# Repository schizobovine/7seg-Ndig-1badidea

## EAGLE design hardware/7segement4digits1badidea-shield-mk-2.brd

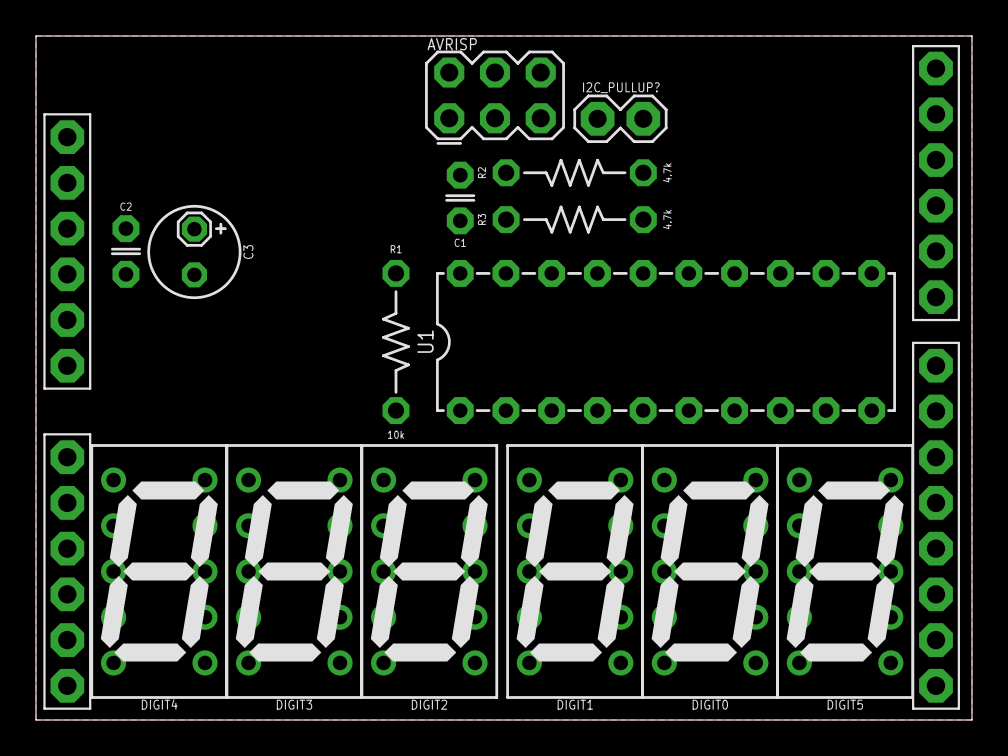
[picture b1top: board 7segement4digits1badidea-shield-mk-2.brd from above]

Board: 2 copper layers, 52.0 x 38.0 mm, 16 parts (0 on the bottom side), 21 nets, no tracks yet.

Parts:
AVRISP: AVR_SPI_PRG_6PTH; 2X3
C1: 0.1uF; C025-024X044
C2: 1uF; C025-024X044
C3: 10uF; E2,5-5
DIGIT0, DIGIT1, DIGIT2, DIGIT3, DIGIT4, DIGIT5: 7SEG_1DIGPTH-10MM; 7SEG_1DIG_10MM
I2C_PULLUP?: M02PTH; 1X02
R1: 10k; RESISTOR-AXIAL-PTH-7.68MM
R2, R3: 4.7k; RESISTOR-AXIAL-PTH-7.68MM
U1: ATTINY4213; DIL20
U2: ARDUINO_SHIELD_NOOUTLINE_INSIDE_SMALLER

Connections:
A: DIGIT0.10, DIGIT1.10, DIGIT2.10, DIGIT3.10, DIGIT4.10, DIGIT5.10, U1.2
B: DIGIT0.9, DIGIT1.9, DIGIT2.9, DIGIT3.9, DIGIT4.9, DIGIT5.9, U1.3
C: DIGIT0.8, DIGIT1.8, DIGIT2.8, DIGIT3.8, DIGIT4.8, DIGIT5.8, U1.4
D: DIGIT0.5, DIGIT1.5, DIGIT2.5, DIGIT3.5, DIGIT4.5, DIGIT5.5, U1.5
DIG0: DIGIT0.1, DIGIT0.6, U1.11
DIG1: DIGIT1.1, DIGIT1.6, U1.12
DIG2: DIGIT2.1, DIGIT2.6, U1.13
DIG3: DIGIT3.1, DIGIT3.6, U1.14
DIG4: DIGIT4.1, DIGIT4.6, U1.15
DIG5: DIGIT5.1, DIGIT5.6, U1.16
DP: DIGIT0.7, DIGIT1.7, DIGIT2.7, DIGIT3.7, DIGIT4.7, DIGIT5.7, U1.9
E: DIGIT0.4, DIGIT1.4, DIGIT2.4, DIGIT3.4, DIGIT4.4, DIGIT5.4, U1.6
F: DIGIT0.2, DIGIT1.2, DIGIT2.2, DIGIT3.2, DIGIT4.2, DIGIT5.2, U1.7
G: DIGIT0.3, DIGIT1.3, DIGIT2.3, DIGIT3.3, DIGIT4.3, DIGIT5.3, U1.8
GND: AVRISP.6, C1.2, C2.2, C3.-, U1.10, U2.GND@0, U2.GND@1
MISO: AVRISP.1, U1.18
MOSI/SDA: AVRISP.4, R2.P$1, U1.17, U2.A4
unnamed: R1.P$2, U1.1
unnamed: I2C_PULLUP?.2, R2.P$2, R3.P$2
SCK/SCL: AVRISP.3, R3.P$1, U1.19, U2.A5
VCC: AVRISP.2, C1.1, C2.1, C3.+, I2C_PULLUP?.1, R1.P$1, U1.20, U2.5V

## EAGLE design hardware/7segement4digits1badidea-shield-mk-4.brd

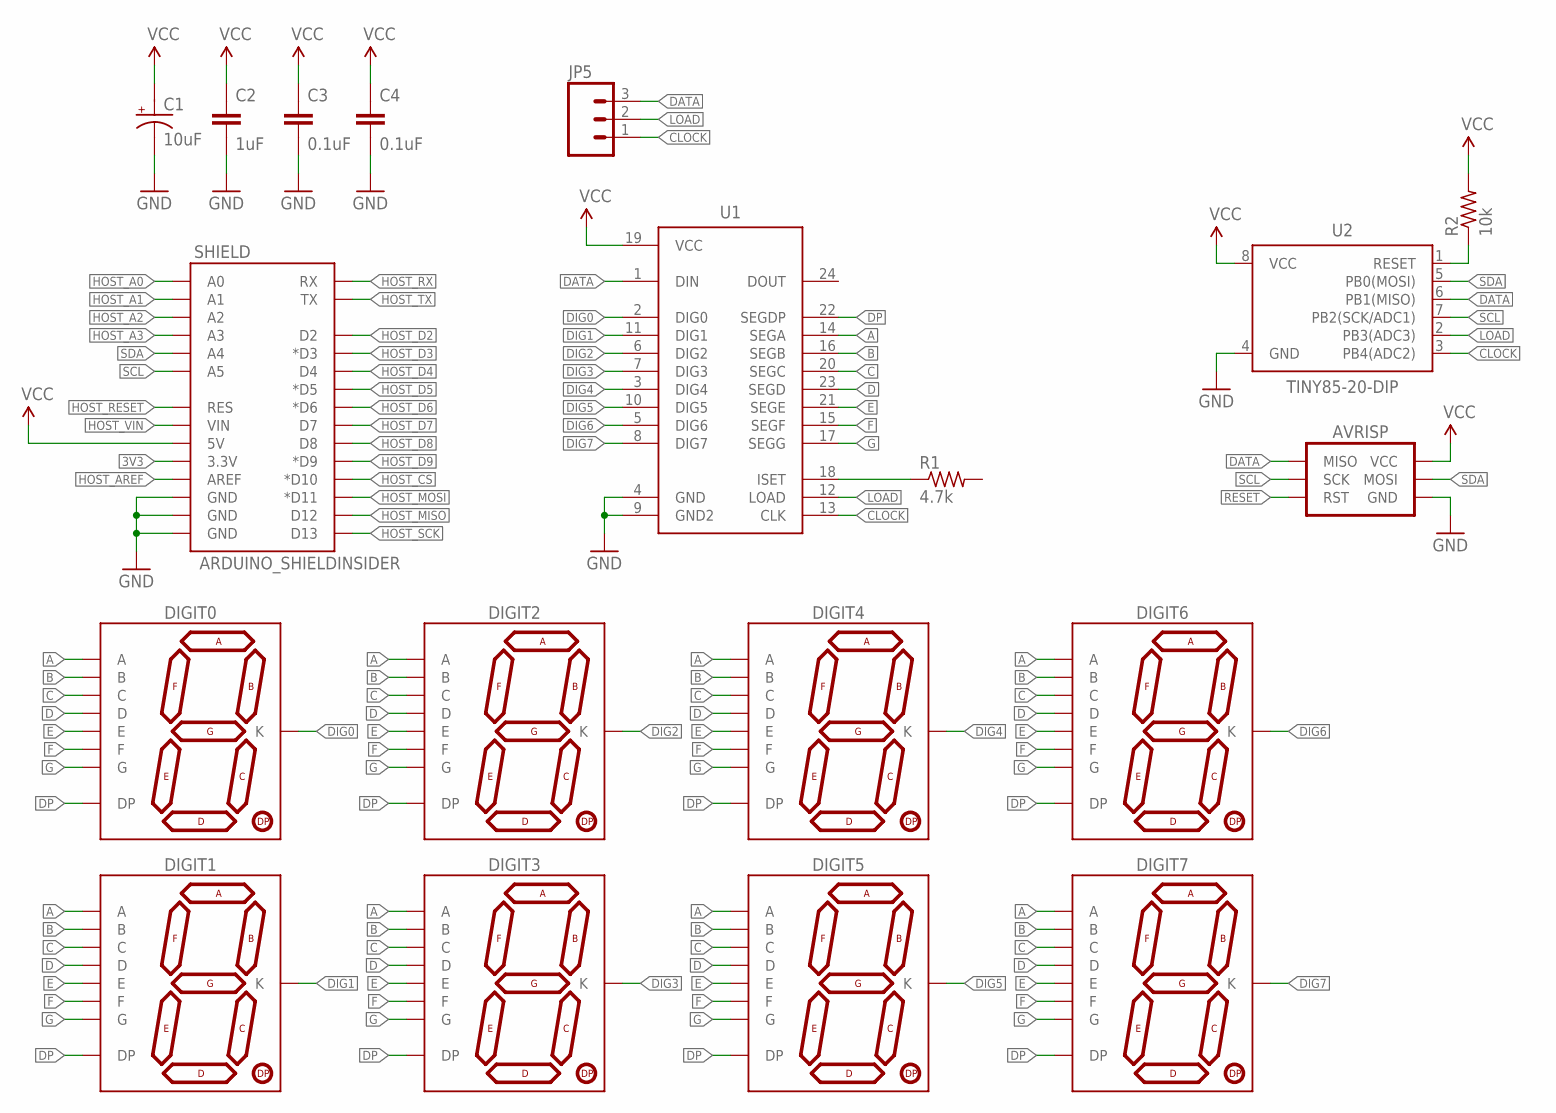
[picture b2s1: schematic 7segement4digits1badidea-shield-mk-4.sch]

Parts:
AVRISP: AVR_SPI_PRG_6PTH; 2X3
C1: 10uF; E2,5-5
C2: 1uF; C025-024X044
C3, C4: 0.1uF; C025-024X044
DIGIT0, DIGIT1, DIGIT2, DIGIT3, DIGIT4, DIGIT5, DIGIT6, DIGIT7: 7SEG_1DIGPTH-10MM; 7SEG_1DIG_10MM
JP5: M03PTH; 1X03
R1: 4.7k; RESISTOR-AXIAL-PTH-7.68MM
R2: 10k; RESISTOR-AXIAL-PTH-7.68MM
SHIELD: ARDUINO_SHIELDINSIDER; ARDUINO_SHIELD_NOOUTLINE_INSIDE
U1: MAX7219DIP; DIL24
U2: TINY85-20-DIP; DIP08

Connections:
3V3: SHIELD.3.3V
A: DIGIT0.10 (A), DIGIT1.10 (A), DIGIT2.10 (A), DIGIT3.10 (A), DIGIT4.10 (A), DIGIT5.10 (A), DIGIT6.10 (A), DIGIT7.10 (A), U1.14 (SEGA)
B: DIGIT0.9 (B), DIGIT1.9 (B), DIGIT2.9 (B), DIGIT3.9 (B), DIGIT4.9 (B), DIGIT5.9 (B), DIGIT6.9 (B), DIGIT7.9 (B), U1.16 (SEGB)
C: DIGIT0.8 (C), DIGIT1.8 (C), DIGIT2.8 (C), DIGIT3.8 (C), DIGIT4.8 (C), DIGIT5.8 (C), DIGIT6.8 (C), DIGIT7.8 (C), U1.20 (SEGC)
CLOCK: JP5.1, U1.13 (CLK), U2.3 (PB4(ADC2))
D: DIGIT0.5 (D), DIGIT1.5 (D), DIGIT2.5 (D), DIGIT3.5 (D), DIGIT4.5 (D), DIGIT5.5 (D), DIGIT6.5 (D), DIGIT7.5 (D), U1.23 (SEGD)
DATA: AVRISP.1 (MISO), JP5.3, U1.1 (DIN), U2.6 (PB1(MISO))
DIG0: DIGIT0.1 (K), DIGIT0.6 (K), U1.2 (DIG0)
DIG1: DIGIT1.1 (K), DIGIT1.6 (K), U1.11 (DIG1)
DIG2: DIGIT2.1 (K), DIGIT2.6 (K), U1.6 (DIG2)
DIG3: DIGIT3.1 (K), DIGIT3.6 (K), U1.7 (DIG3)
DIG4: DIGIT4.1 (K), DIGIT4.6 (K), U1.3 (DIG4)
DIG5: DIGIT5.1 (K), DIGIT5.6 (K), U1.10 (DIG5)
DIG6: DIGIT6.1 (K), DIGIT6.6 (K), U1.5 (DIG6)
DIG7: DIGIT7.1 (K), DIGIT7.6 (K), U1.8 (DIG7)
DP: DIGIT0.7 (DP), DIGIT1.7 (DP), DIGIT2.7 (DP), DIGIT3.7 (DP), DIGIT4.7 (DP), DIGIT5.7 (DP), DIGIT6.7 (DP), DIGIT7.7 (DP), U1.22 (SEGDP)
E: DIGIT0.4 (E), DIGIT1.4 (E), DIGIT2.4 (E), DIGIT3.4 (E), DIGIT4.4 (E), DIGIT5.4 (E), DIGIT6.4 (E), DIGIT7.4 (E), U1.21 (SEGE)
F: DIGIT0.2 (F), DIGIT1.2 (F), DIGIT2.2 (F), DIGIT3.2 (F), DIGIT4.2 (F), DIGIT5.2 (F), DIGIT6.2 (F), DIGIT7.2 (F), U1.15 (SEGF)
G: DIGIT0.3 (G), DIGIT1.3 (G), DIGIT2.3 (G), DIGIT3.3 (G), DIGIT4.3 (G), DIGIT5.3 (G), DIGIT6.3 (G), DIGIT7.3 (G), U1.17 (SEGG)
GND: AVRISP.6 (GND), C1.-, C2.2, C3.2, C4.2, SHIELD.GND@0 (GND), SHIELD.GND@1 (GND), SHIELD.GND@2 (GND), U1.4 (GND), U1.9 (GND2), U2.4 (GND)
HOST_A0: SHIELD.A0
HOST_A1: SHIELD.A1
HOST_A2: SHIELD.A2
HOST_A3: SHIELD.A3
HOST_AREF: SHIELD.AREF
HOST_CS: SHIELD.D10 (*D10)
HOST_D2: SHIELD.D2
HOST_D3: SHIELD.D3 (*D3)
HOST_D4: SHIELD.D4
HOST_D5: SHIELD.D5 (*D5)
HOST_D6: SHIELD.D6 (*D6)
HOST_D7: SHIELD.D7
HOST_D8: SHIELD.D8
HOST_D9: SHIELD.D9 (*D9)
HOST_MISO: SHIELD.D12
HOST_MOSI: SHIELD.D11 (*D11)
HOST_RESET: SHIELD.RES
HOST_RX: SHIELD.RX
HOST_SCK: SHIELD.D13
HOST_TX: SHIELD.TX
HOST_VIN: SHIELD.VIN
LOAD: JP5.2, U1.12 (LOAD), U2.2 (PB3(ADC3))
unnamed: R2.P$1 (1), U2.1 (RESET)
unnamed: R1.P$1 (1), U1.18 (ISET)
RESET: AVRISP.5 (RST)
SCL: AVRISP.3 (SCK), SHIELD.A5, U2.7 (PB2(SCK/ADC1))
SDA: AVRISP.4 (MOSI), SHIELD.A4, U2.5 (PB0(MOSI))
VCC: AVRISP.2 (VCC), C1.+, C2.1, C3.1, C4.1, R2.P$2 (2), SHIELD.5V, U1.19 (VCC), U2.8 (VCC)

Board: 2 copper layers, 19 parts (0 on the bottom side), 25 nets, no tracks yet.

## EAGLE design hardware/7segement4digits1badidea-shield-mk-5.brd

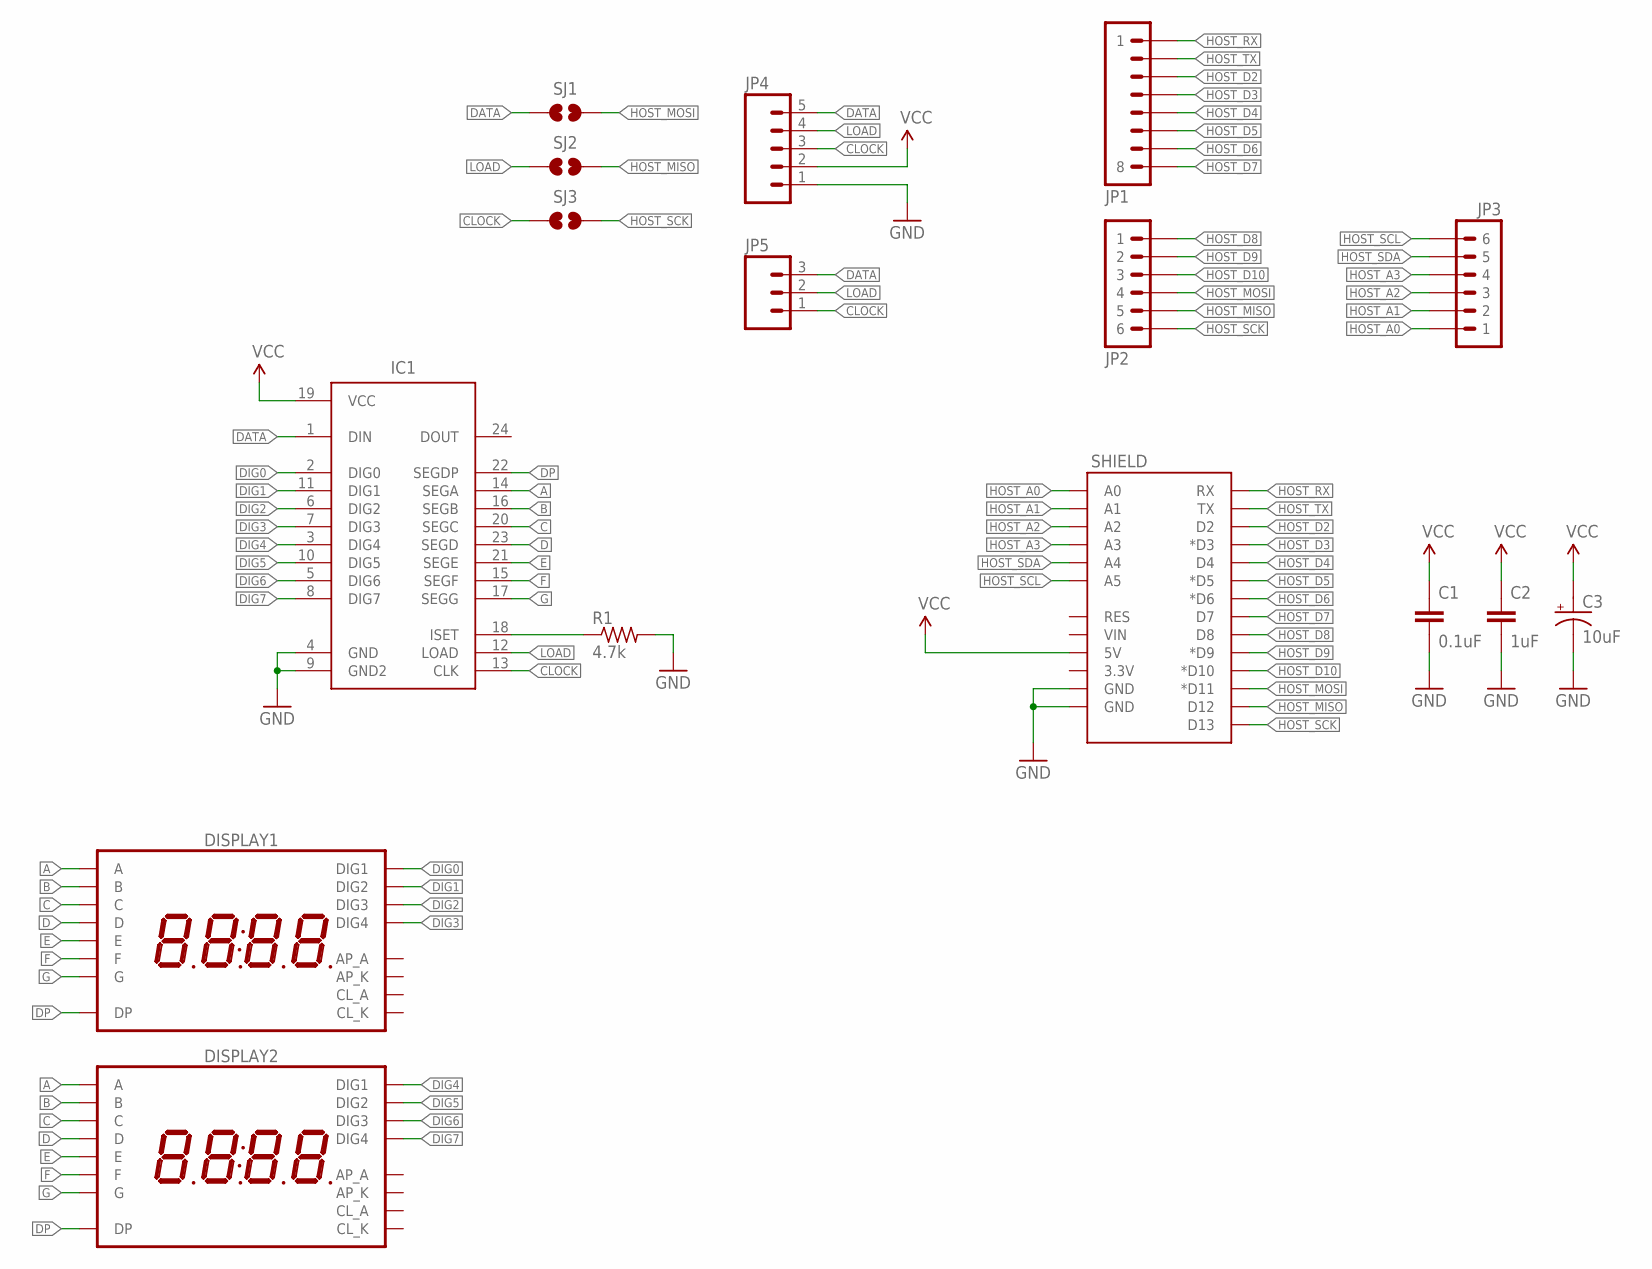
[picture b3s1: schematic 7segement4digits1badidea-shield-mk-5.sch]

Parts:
C1: 0.1uF; C025-024X044
C2: 1uF; C025-024X044
C3: 10uF; E2,5-6
DISPLAY1, DISPLAY2: 7SEG_4DIGIT_10MM; 7SEG_4DIG_10MM
IC1: MAX7219DIP; DIL24
JP1: M08NOT-SHITTY-NO-SILK; 1X08_NS
JP2, JP3: M06SIP; 1X06
JP4: M05PTH; 1X05
JP5: M031X03_NO_SILK; 1X03_NO_SILK
R1: 4.7k; RESISTOR-AXIAL-PTH-5.08MM
SHIELD: ARDUINO_SHIELD_SMALLERNEKKID; ARDUINO_SHIELD_SMALLER_NEKKID
SJ1, SJ2, SJ3: JUMPER-PAD-2-NOYES_SILK; PAD-JUMPER-2-NO_YES_SILK

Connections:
A: DISPLAY1.14 (A), DISPLAY2.14 (A), IC1.14 (SEGA)
B: DISPLAY1.16 (B), DISPLAY2.16 (B), IC1.16 (SEGB)
C: DISPLAY1.13 (C), DISPLAY2.13 (C), IC1.20 (SEGC)
CLOCK: IC1.13 (CLK), JP4.3, JP5.1, SJ3.1
D: DISPLAY1.3 (D), DISPLAY2.3 (D), IC1.23 (SEGD)
DATA: IC1.1 (DIN), JP4.5, JP5.3, SJ1.1
DIG0: DISPLAY1.1 (DIG1), IC1.2 (DIG0)
DIG1: DISPLAY1.2 (DIG2), IC1.11 (DIG1)
DIG2: DISPLAY1.6 (DIG3), IC1.6 (DIG2)
DIG3: DISPLAY1.8 (DIG4), IC1.7 (DIG3)
DIG4: DISPLAY2.1 (DIG1), IC1.3 (DIG4)
DIG5: DISPLAY2.2 (DIG2), IC1.10 (DIG5)
DIG6: DISPLAY2.6 (DIG3), IC1.5 (DIG6)
DIG7: DISPLAY2.8 (DIG4), IC1.8 (DIG7)
DP: DISPLAY1.7 (DP), DISPLAY2.7 (DP), IC1.22 (SEGDP)
E: DISPLAY1.5 (E), DISPLAY2.5 (E), IC1.21 (SEGE)
F: DISPLAY1.11 (F), DISPLAY2.11 (F), IC1.15 (SEGF)
G: DISPLAY1.15 (G), DISPLAY2.15 (G), IC1.17 (SEGG)
GND: C1.2, C2.2, C3.-, IC1.4 (GND), IC1.9 (GND2), JP4.1, R1.P$2 (2), SHIELD.GND@0 (GND), SHIELD.GND@1 (GND)
HOST_A0: JP3.1, SHIELD.A0
HOST_A1: JP3.2, SHIELD.A1
HOST_A2: JP3.3, SHIELD.A2
HOST_A3: JP3.4, SHIELD.A3
HOST_D2: JP1.3, SHIELD.D2
HOST_D3: JP1.4, SHIELD.D3 (*D3)
HOST_D4: JP1.5, SHIELD.D4
HOST_D5: JP1.6, SHIELD.D5 (*D5)
HOST_D6: JP1.7, SHIELD.D6 (*D6)
HOST_D7: JP1.8, SHIELD.D7
HOST_D8: JP2.1, SHIELD.D8
HOST_D9: JP2.2, SHIELD.D9 (*D9)
HOST_D10: JP2.3, SHIELD.D10 (*D10)
HOST_MISO: JP2.5, SHIELD.D12, SJ2.2
HOST_MOSI: JP2.4, SHIELD.D11 (*D11), SJ1.2
HOST_RX: JP1.1, SHIELD.RX
HOST_SCK: JP2.6, SHIELD.D13, SJ3.2
HOST_SCL: JP3.6, SHIELD.A5
HOST_SDA: JP3.5, SHIELD.A4
HOST_TX: JP1.2, SHIELD.TX
LOAD: IC1.12 (LOAD), JP4.4, JP5.2, SJ2.1
unnamed: IC1.18 (ISET), R1.P$1 (1)
VCC: C1.1, C2.1, C3.+, IC1.19 (VCC), JP4.2, SHIELD.5V

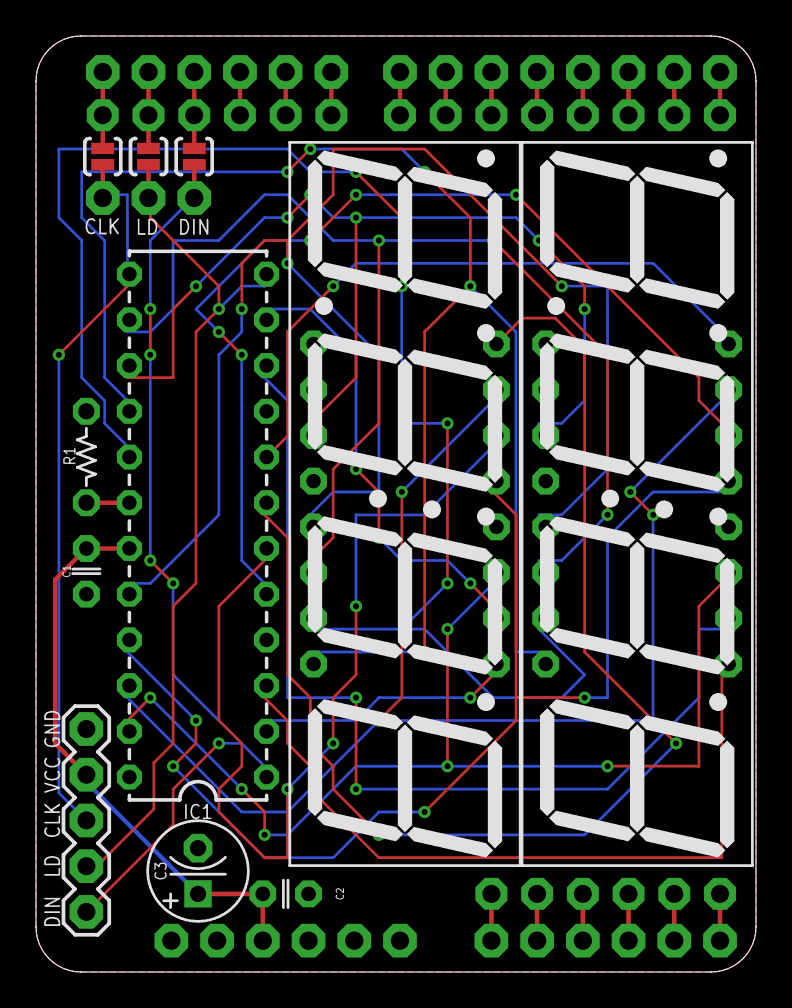
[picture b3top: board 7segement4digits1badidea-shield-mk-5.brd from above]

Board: 2 copper layers, 40.0 x 52.0 mm, 16 parts (0 on the bottom side), 42 nets.

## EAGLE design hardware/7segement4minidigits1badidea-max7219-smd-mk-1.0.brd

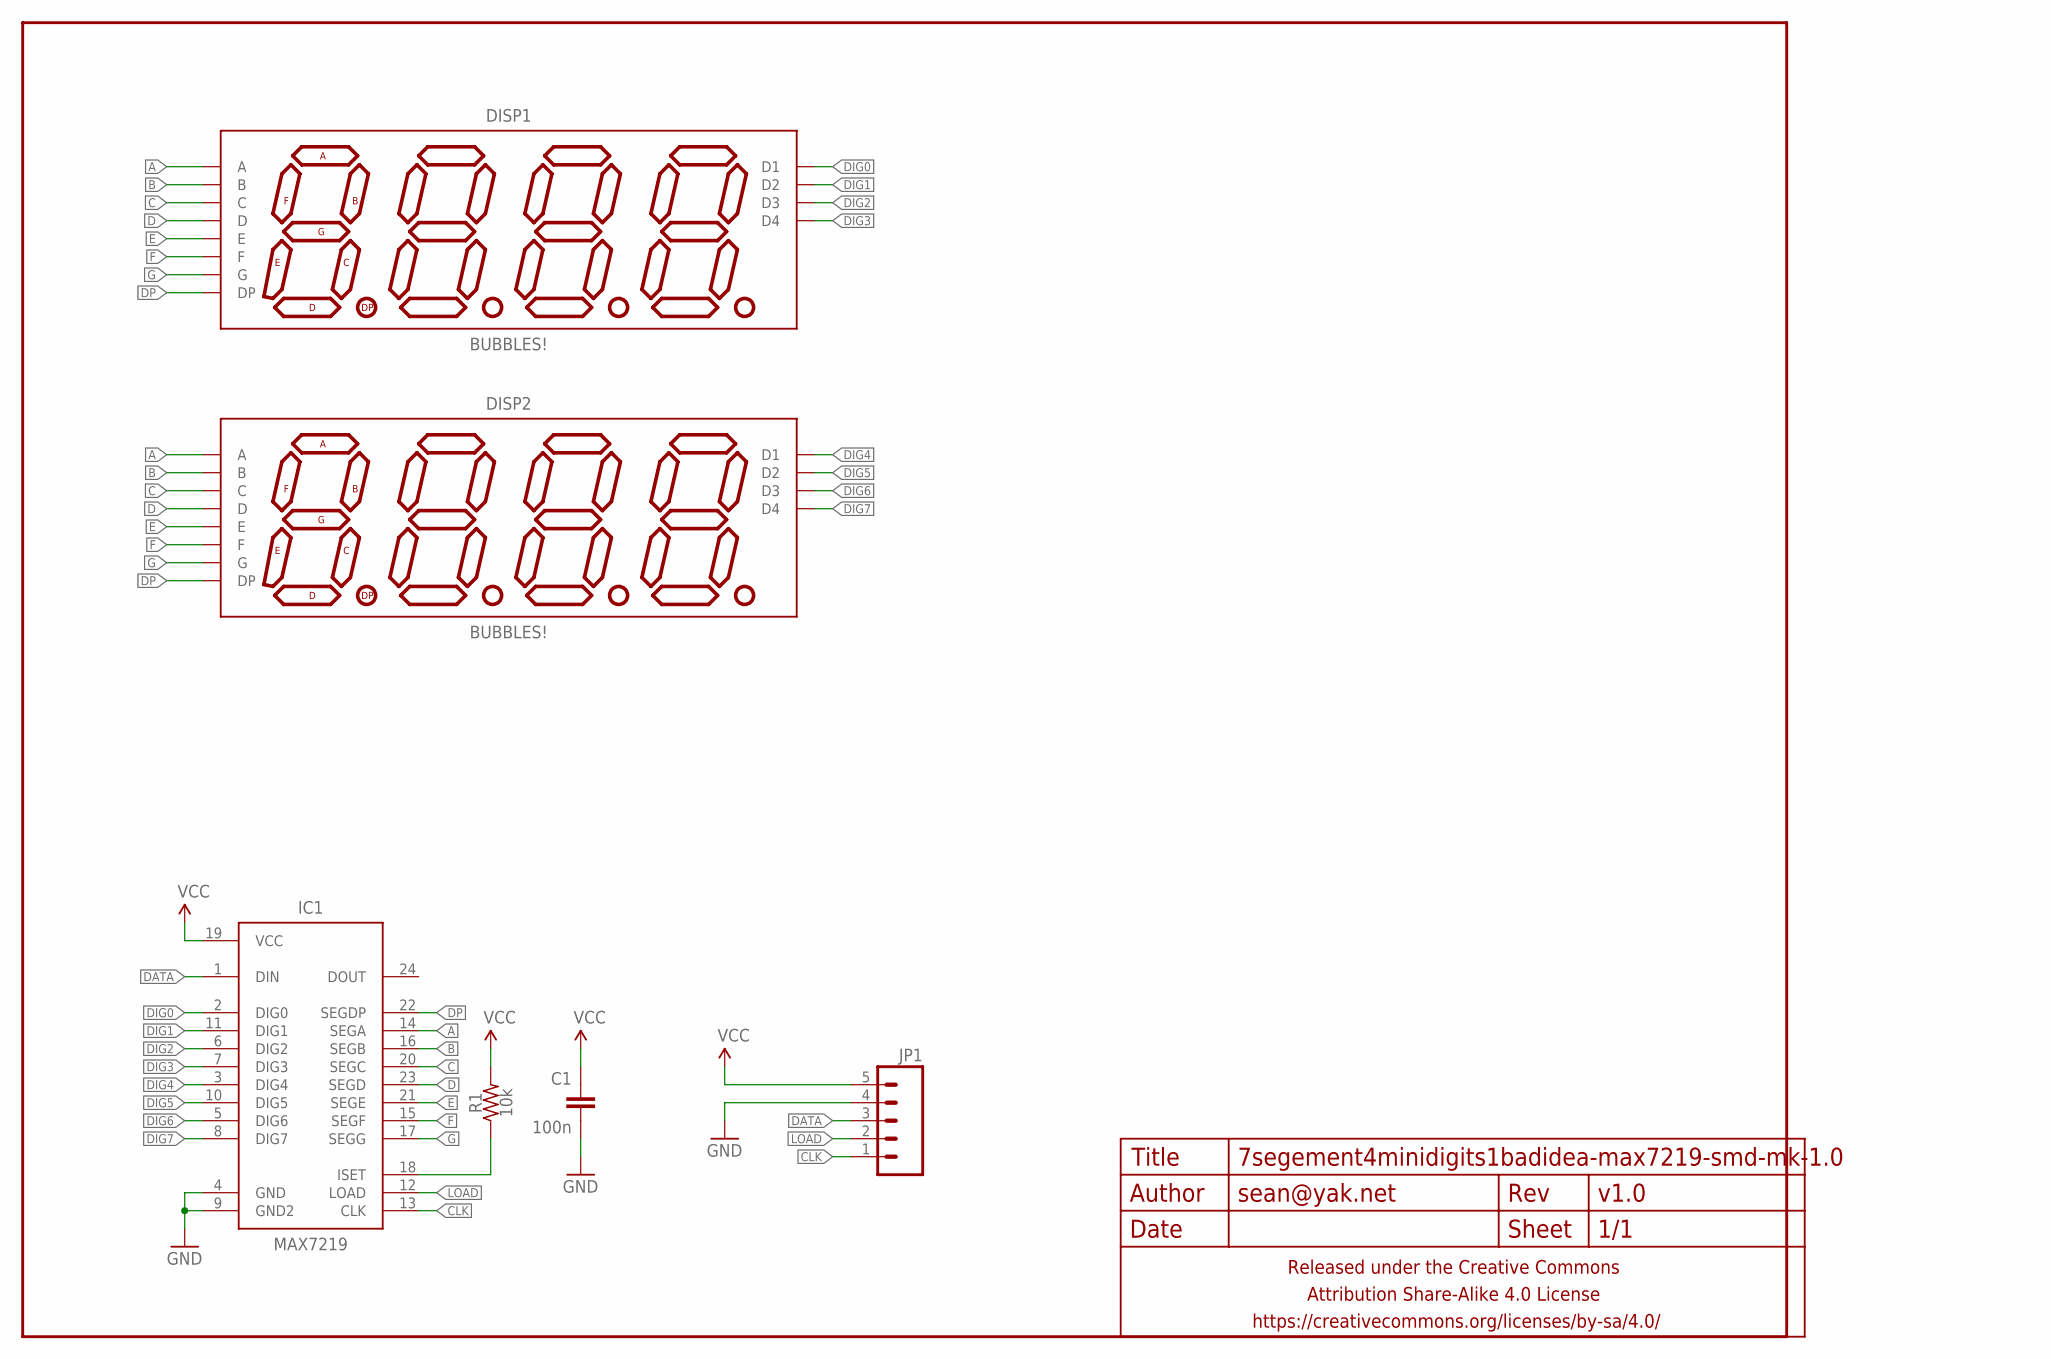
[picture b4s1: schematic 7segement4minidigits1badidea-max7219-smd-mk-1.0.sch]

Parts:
C1: 100n; C0603
DISP1, DISP2: BUBBLES!; DIL12
FRAME1: FRAME-LETTERNO_PACKAGE; DUMMY
IC1: MAX7219; SO24W
JP1: M05PTH-CENTERED; 1X05_PTH_CENTERED
R1: 10k; R0603

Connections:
A: DISP1.12 (A), DISP2.12 (A), IC1.14 (SEGA)
B: DISP1.11 (B), DISP2.11 (B), IC1.16 (SEGB)
C: DISP1.3 (C), DISP2.3 (C), IC1.20 (SEGC)
CLK: IC1.13 (CLK), JP1.1
D: DISP1.8 (D), DISP2.8 (D), IC1.23 (SEGD)
DATA: IC1.1 (DIN), JP1.3
DIG0: DISP1.1 (D1), IC1.2 (DIG0)
DIG1: DISP1.10 (D2), IC1.11 (DIG1)
DIG2: DISP1.4 (D3), IC1.6 (DIG2)
DIG3: DISP1.6 (D4), IC1.7 (DIG3)
DIG4: DISP2.1 (D1), IC1.3 (DIG4)
DIG5: DISP2.10 (D2), IC1.10 (DIG5)
DIG6: DISP2.4 (D3), IC1.5 (DIG6)
DIG7: DISP2.6 (D4), IC1.8 (DIG7)
DP: DISP1.5 (DP), DISP2.5 (DP), IC1.22 (SEGDP)
E: DISP1.2 (E), DISP2.2 (E), IC1.21 (SEGE)
F: DISP1.9 (F), DISP2.9 (F), IC1.15 (SEGF)
G: DISP1.7 (G), DISP2.7 (G), IC1.17 (SEGG)
GND: C1.2, IC1.4 (GND), IC1.9 (GND2), JP1.4
LOAD: IC1.12 (LOAD), JP1.2
unnamed: IC1.18 (ISET), R1.1
VCC: C1.1, IC1.19 (VCC), JP1.5, R1.2

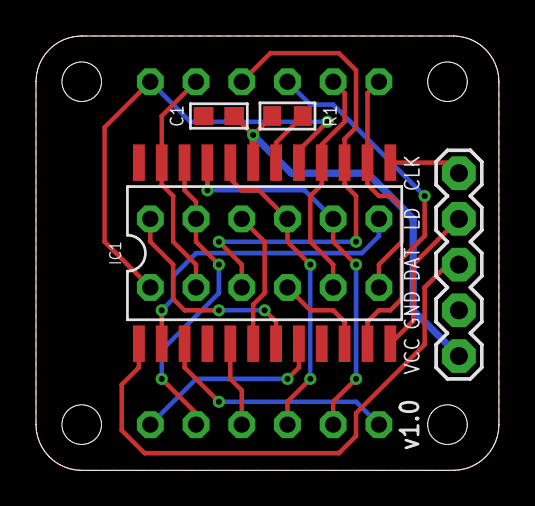
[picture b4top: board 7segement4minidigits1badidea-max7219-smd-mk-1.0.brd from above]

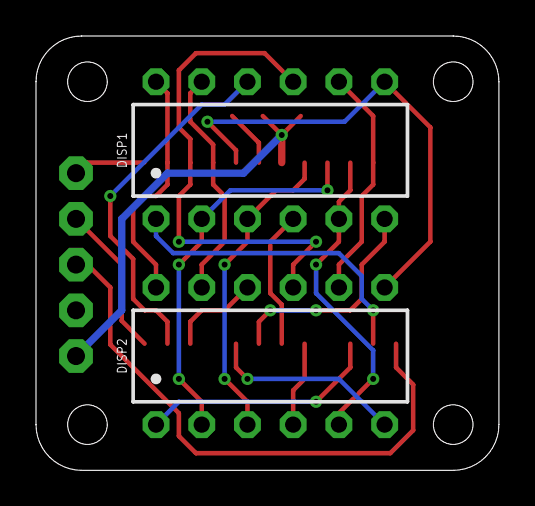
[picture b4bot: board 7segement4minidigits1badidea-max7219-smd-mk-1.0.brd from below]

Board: 2 copper layers, 25.7 x 24.1 mm, 7 parts (2 on the bottom side), 22 nets.

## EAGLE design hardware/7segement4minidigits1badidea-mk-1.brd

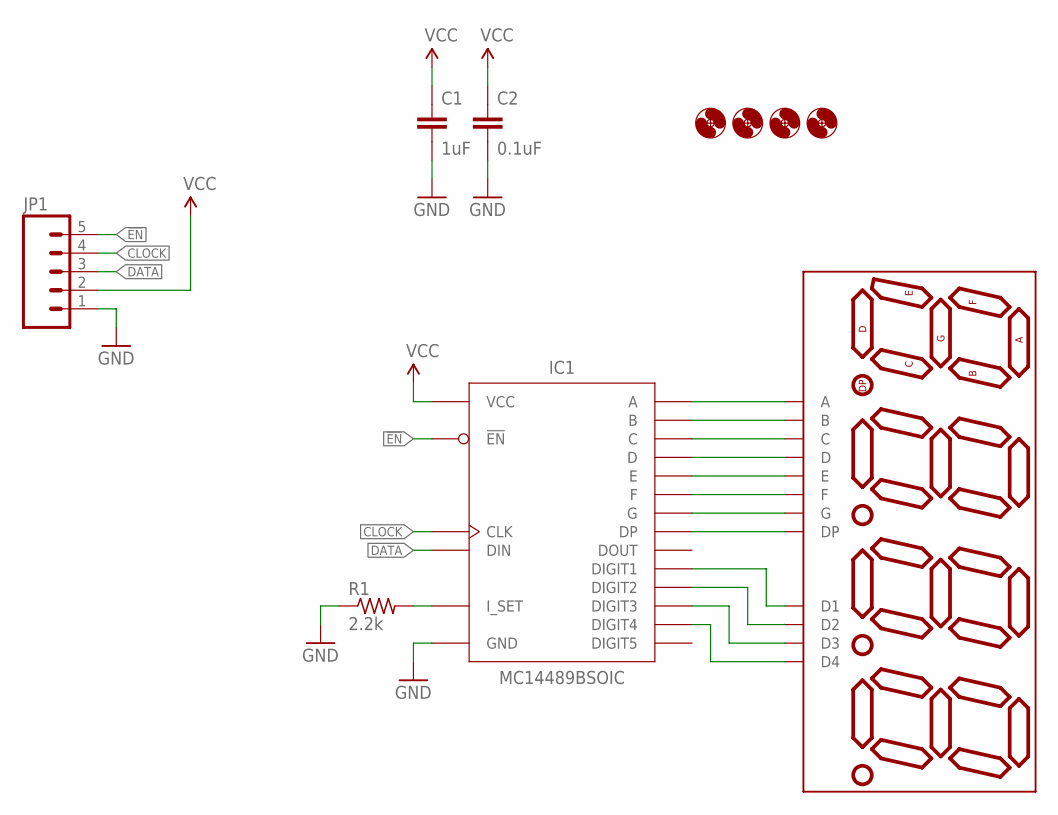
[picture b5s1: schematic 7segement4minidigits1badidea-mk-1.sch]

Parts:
C1: 1uF; C025-024X044
C2: 0.1uF; C025-024X044
DISP1: BUBBLES!; DIL12
H1, H2, H3, H4: HOLE#2; HOLE-#2
IC1: MC14489BSOIC; SOP20W
JP1: M05PTH; 1X05
R1: 2.2k; RESISTOR-AXIAL-PTH-5.08MM

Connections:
!EN: IC1.10 (!EN), JP1.5
CLOCK: IC1.11 (CLK), JP1.4
DATA: IC1.12 (DIN), JP1.3
GND: C1.2, C2.2, IC1.14 (GND), JP1.1, R1.P$1 (1)
unnamed: DISP1.12 (A), IC1.7 (A)
unnamed: DISP1.11 (B), IC1.6 (B)
unnamed: DISP1.3 (C), IC1.5 (C)
unnamed: DISP1.8 (D), IC1.4 (D)
unnamed: DISP1.2 (E), IC1.2 (E)
unnamed: DISP1.9 (F), IC1.1 (F)
unnamed: DISP1.7 (G), IC1.20 (G)
unnamed: DISP1.5 (DP), IC1.19 (DP)
unnamed: DISP1.1 (D1), IC1.9 (DIGIT1)
unnamed: DISP1.10 (D2), IC1.13 (DIGIT2)
unnamed: DISP1.4 (D3), IC1.15 (DIGIT3)
unnamed: DISP1.6 (D4), IC1.16 (DIGIT4)
unnamed: IC1.8 (I_SET), R1.P$2 (2)
VCC: C1.1, C2.1, IC1.3 (VCC), JP1.2

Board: 2 copper layers, 10 parts (1 on the bottom side), 18 nets, no tracks yet.

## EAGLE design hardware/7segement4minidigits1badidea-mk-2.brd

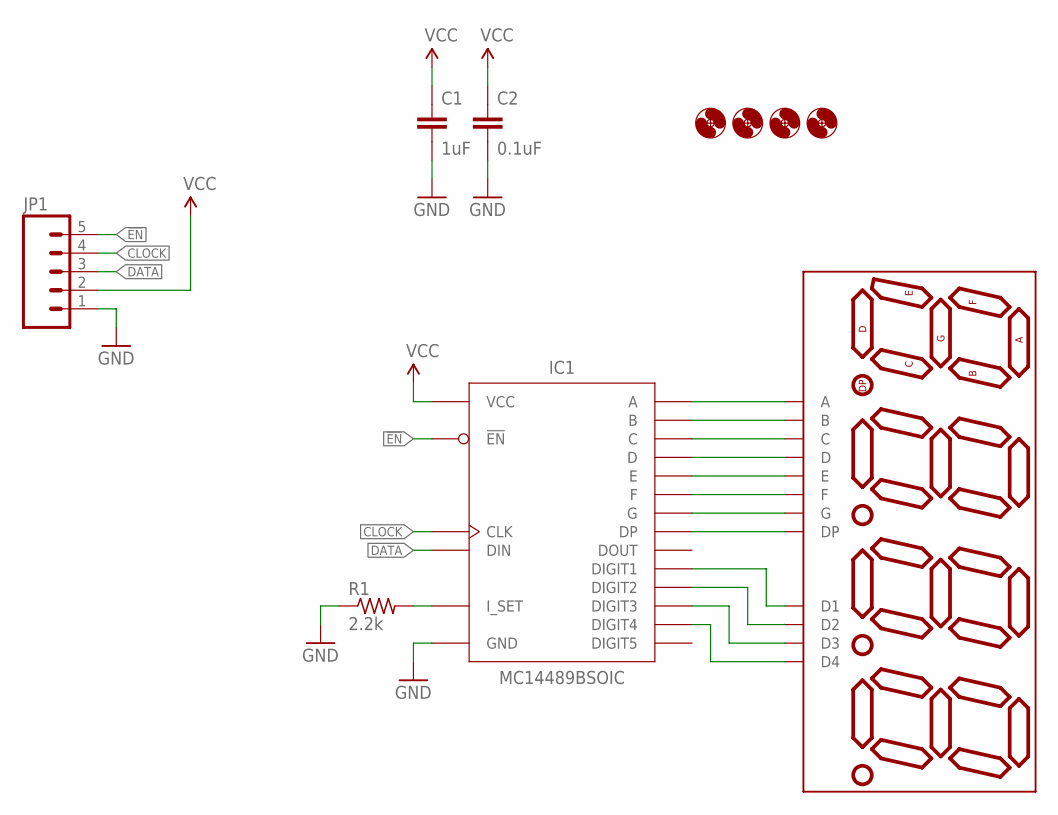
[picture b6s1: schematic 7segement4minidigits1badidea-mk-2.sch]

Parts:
BUBBLES!: (>^_^)>; DIP12-SMD-WAT
C1: 1uF; C0805
C2: 0.1uF; C0603
H1, H2, H3, H4: HOLE#2; HOLE-#2
IC1: MC14489BSOIC; SOP20W
JP1: M05PTH; 1X05
R1: 2.2k; R0603

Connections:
!EN: IC1.10 (!EN), JP1.5
CLOCK: IC1.11 (CLK), JP1.4
DATA: IC1.12 (DIN), JP1.3
GND: C1.2, C2.2, IC1.14 (GND), JP1.1, R1.1
unnamed: BUBBLES!.12 (A), IC1.7 (A)
unnamed: BUBBLES!.11 (B), IC1.6 (B)
unnamed: BUBBLES!.3 (C), IC1.5 (C)
unnamed: BUBBLES!.8 (D), IC1.4 (D)
unnamed: BUBBLES!.2 (E), IC1.2 (E)
unnamed: BUBBLES!.9 (F), IC1.1 (F)
unnamed: BUBBLES!.7 (G), IC1.20 (G)
unnamed: BUBBLES!.5 (DP), IC1.19 (DP)
unnamed: BUBBLES!.1 (D1), IC1.9 (DIGIT1)
unnamed: BUBBLES!.10 (D2), IC1.13 (DIGIT2)
unnamed: BUBBLES!.4 (D3), IC1.15 (DIGIT3)
unnamed: BUBBLES!.6 (D4), IC1.16 (DIGIT4)
unnamed: IC1.8 (I_SET), R1.2
VCC: C1.1, C2.1, IC1.3 (VCC), JP1.2

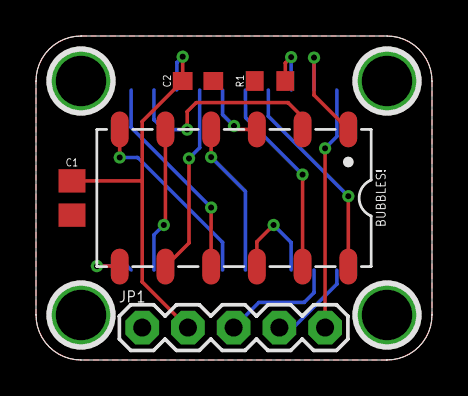
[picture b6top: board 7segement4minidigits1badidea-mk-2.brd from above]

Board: 2 copper layers, 22.0 x 18.0 mm, 10 parts (1 on the bottom side), 18 nets.

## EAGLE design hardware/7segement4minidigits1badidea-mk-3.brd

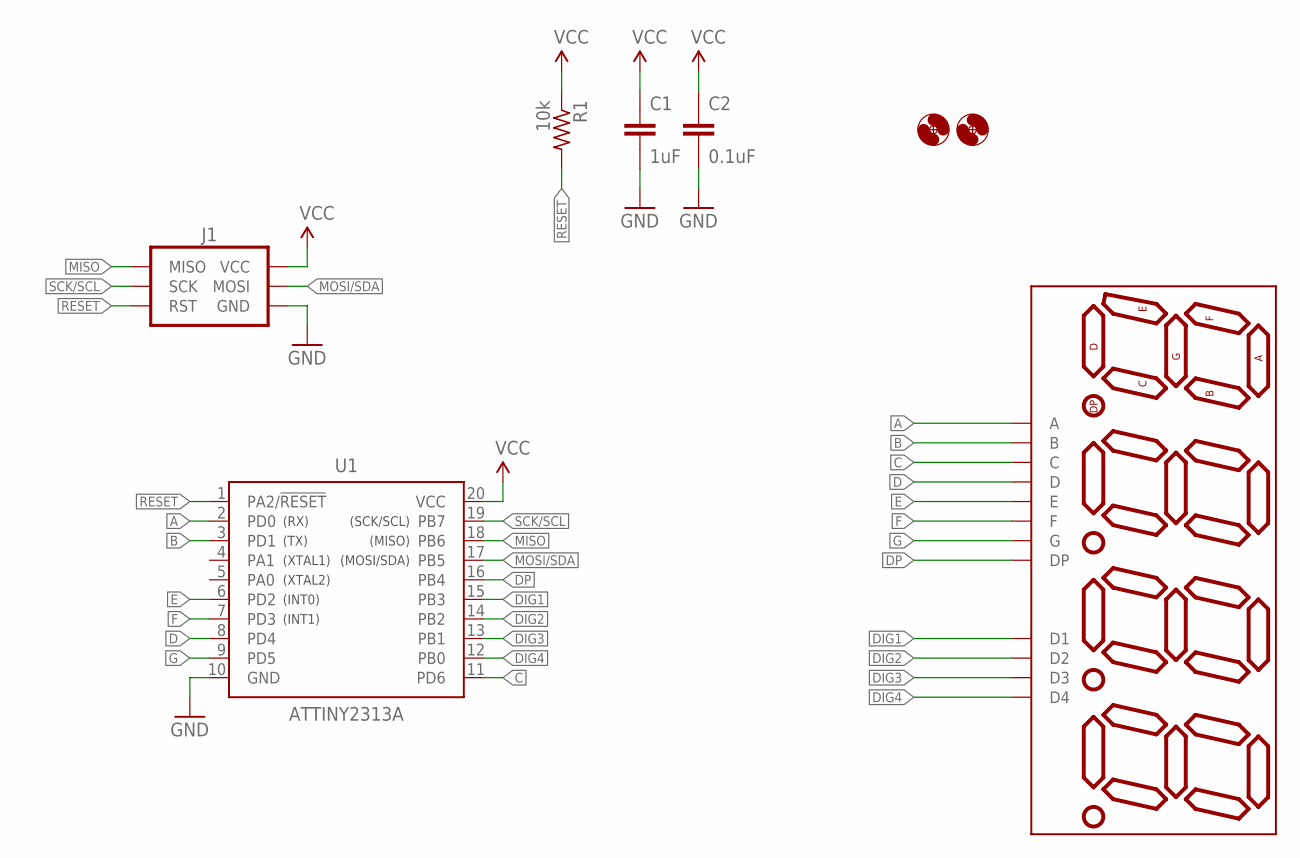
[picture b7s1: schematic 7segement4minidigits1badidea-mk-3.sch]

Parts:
BUBBLES!: (>^_^)>; DIP12-SMD-WAT
C1: 1uF; C0805
C2: 0.1uF; C0603
H1, H2: HOLE#2; HOLE-#2
J1: AVR_SPI_PRG_6PTH_INLINE_I2C; AVR_ISP_INLINE_PTH_I2C
R1: 10k; R0603
U1: ATTINY2313A; SOP20W

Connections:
A: BUBBLES!.12 (A), U1.2 (PD0)
B: BUBBLES!.11 (B), U1.3 (PD1)
C: BUBBLES!.3 (C), U1.11 (PD6)
D: BUBBLES!.8 (D), U1.8 (PD4)
DIG1: BUBBLES!.1 (D1), U1.15 (PB3)
DIG2: BUBBLES!.10 (D2), U1.14 (PB2)
DIG3: BUBBLES!.4 (D3), U1.13 (PB1)
DIG4: BUBBLES!.6 (D4), U1.12 (PB0)
DP: BUBBLES!.5 (DP), U1.16 (PB4)
E: BUBBLES!.2 (E), U1.6 (PD2)
F: BUBBLES!.9 (F), U1.7 (PD3)
G: BUBBLES!.7 (G), U1.9 (PD5)
GND: C1.2, C2.2, J1.GND, U1.10 (GND)
MISO: J1.MISO, U1.18 (PB6)
MOSI/SDA: J1.MOSI, U1.17 (PB5)
RESET: J1.RESET (RST), R1.2, U1.1 (PA2/!RESET)
SCK/SCL: J1.SCK, U1.19 (PB7)
VCC: C1.1, C2.1, J1.VCC, R1.1, U1.20 (VCC)

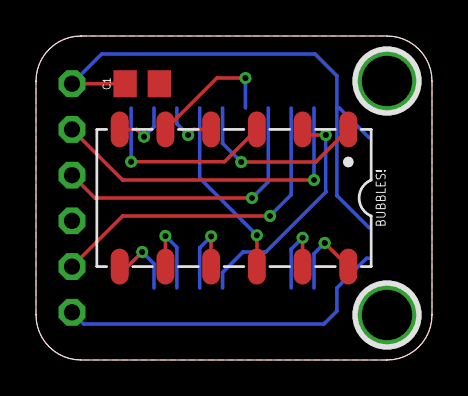
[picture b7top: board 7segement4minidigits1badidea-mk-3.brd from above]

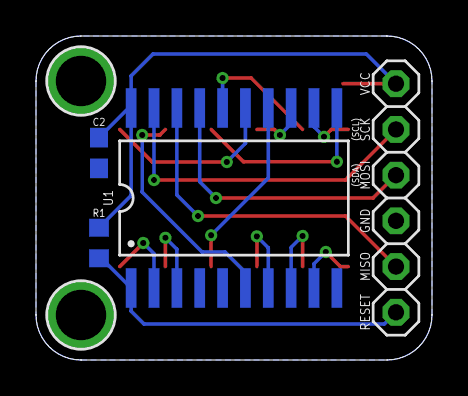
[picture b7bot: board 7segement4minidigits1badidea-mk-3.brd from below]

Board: 2 copper layers, 22.0 x 18.0 mm, 8 parts (4 on the bottom side), 18 nets.

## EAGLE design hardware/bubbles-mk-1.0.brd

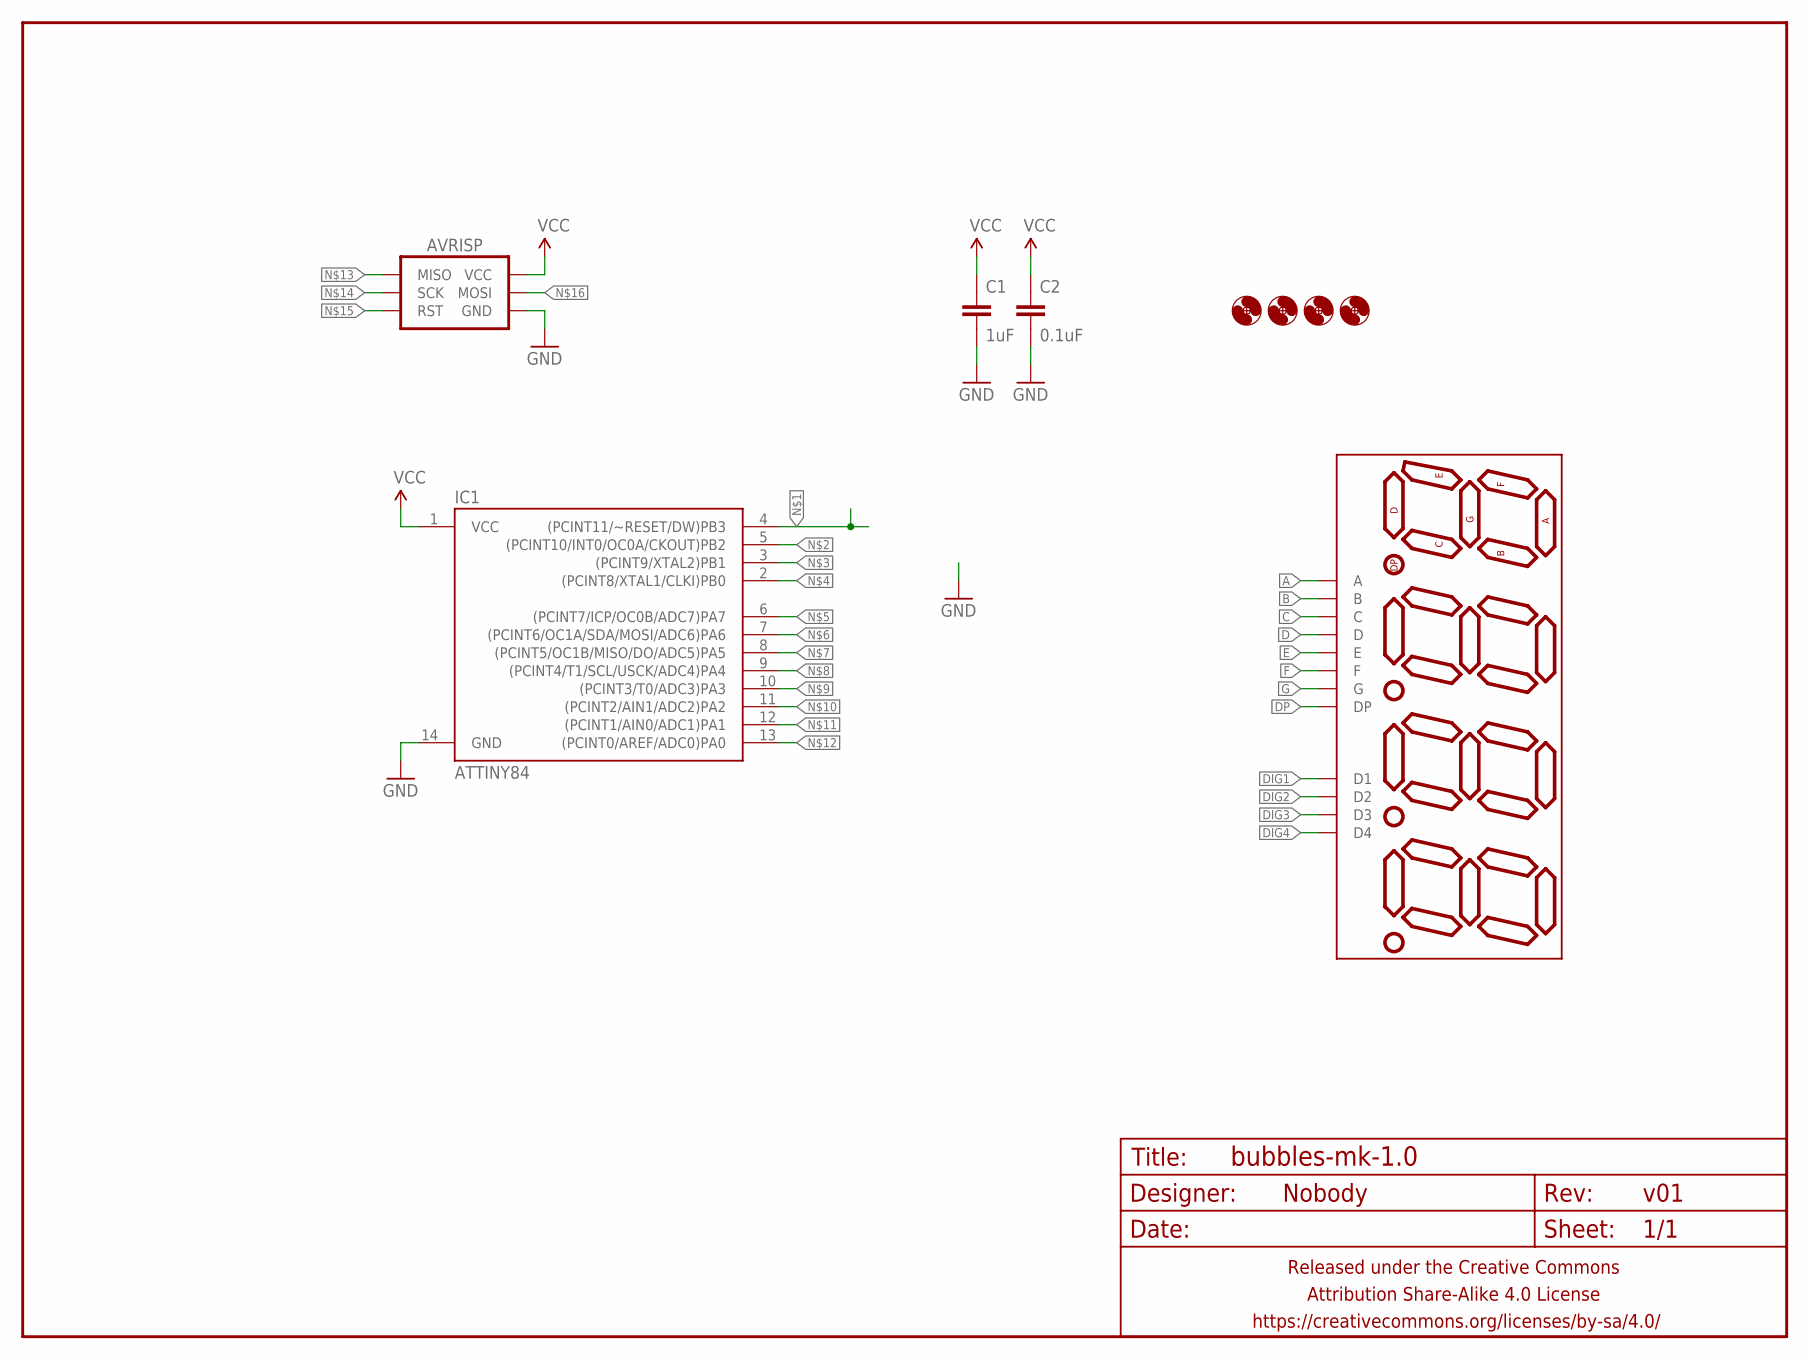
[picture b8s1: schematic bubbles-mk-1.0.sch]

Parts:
AVRISP: AVR_SPI_PRG_6AVR-JST-PTH-RA-I2C; AVR-JST-6-PTH-RA-I2C
C1: 1uF; C025-024X044
C2: 0.1uF; C025-024X044
DISP1: BUBBLES!; DIL12
FRAME1: FRAME-LETTERNO_PACKAGE; DUMMY
H1, H2, H3, H4: HOLE#2; HOLE-#2
IC1: ATTINY84; SO14

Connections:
A: DISP1.12 (A)
B: DISP1.11 (B)
C: DISP1.3 (C)
D: DISP1.8 (D)
DIG1: DISP1.1 (D1)
DIG2: DISP1.10 (D2)
DIG3: DISP1.4 (D3)
DIG4: DISP1.6 (D4)
DP: DISP1.5 (DP)
E: DISP1.2 (E)
F: DISP1.9 (F)
G: DISP1.7 (G)
GND: C1.2, C2.2, IC1.14 (GND)
VCC: C1.1, C2.1, IC1.1 (VCC)

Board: 2 copper layers, 10 parts (0 on the bottom side), 2 nets, no tracks yet.

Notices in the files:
parts and their libraries:
A_butts: Released under the Creative Commons Attribution Share-Alike 4.0 License
A_butts: https://creativecommons.org/licenses/by-sa/4.0
A_butts: Released under the Creative Commons
